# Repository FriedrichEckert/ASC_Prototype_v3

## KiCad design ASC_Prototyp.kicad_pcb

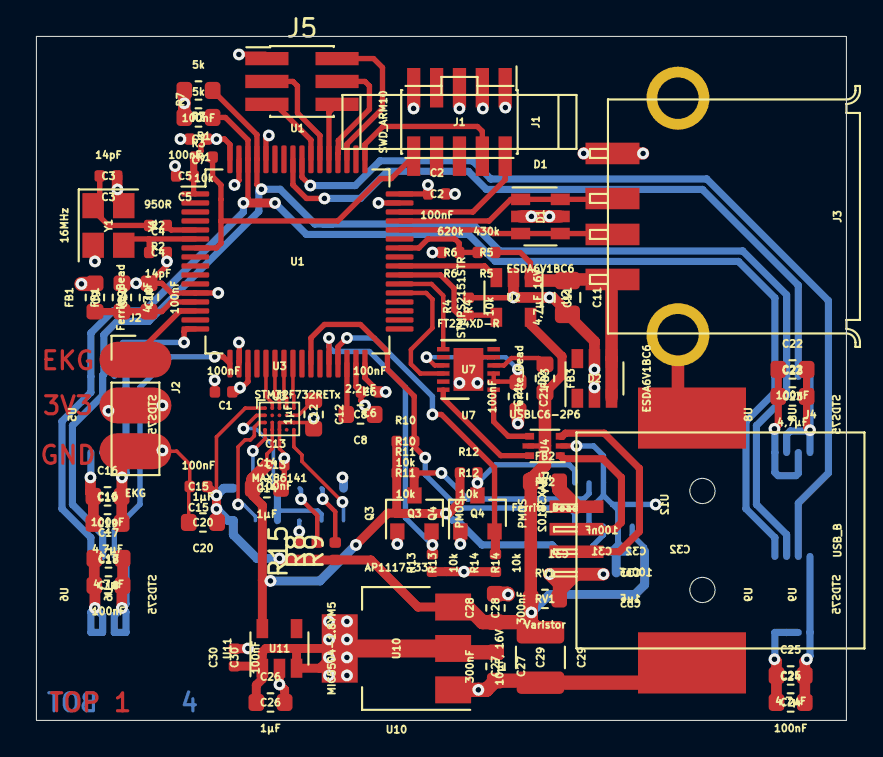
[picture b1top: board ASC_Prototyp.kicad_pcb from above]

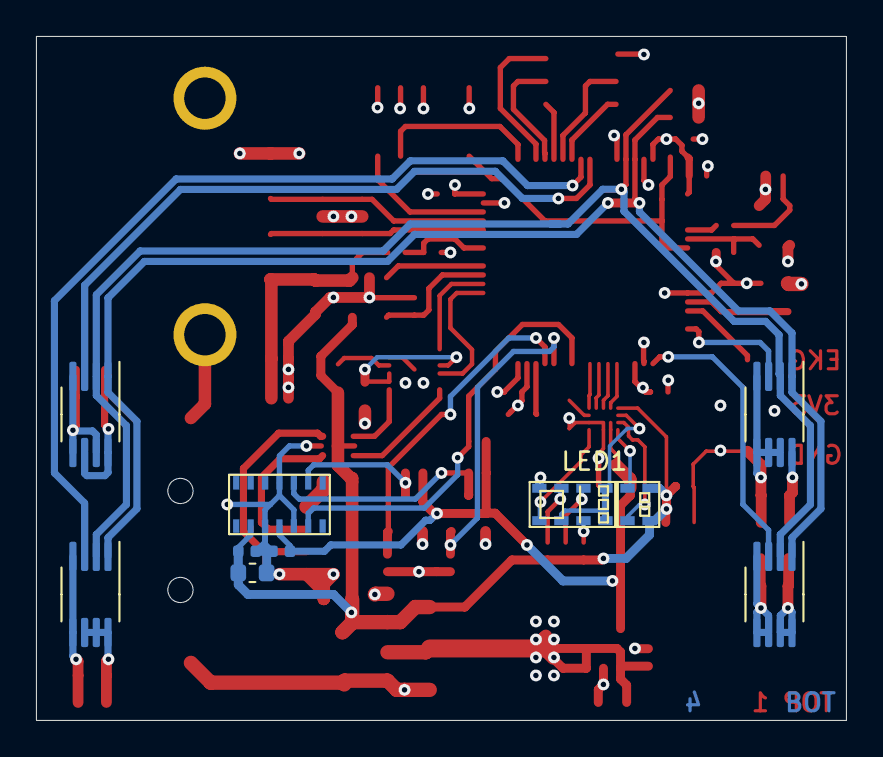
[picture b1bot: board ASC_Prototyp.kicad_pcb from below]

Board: 4 copper layers, 45.0 x 38.0 mm, 75 parts (9 on the bottom side), 56 nets.

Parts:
C1, C2, C5, C6, C7, C13, C15, C30, C31, C32: 100nF; C_0402_1005Metric
C3, C4: 14pF; C_0402_1005Metric
C8: 2,2µF; C_0603_1608Metric
C9, C17, C19, C23, C25: 4,7µF; C_0603_1608Metric
C10, C16, C18, C21, C22, C24: 100nF; C_0603_1608Metric
C11: 4,7µF 16V; C_0805_2012Metric
C12, C14, C20, C26, C33: 1µF; C_0603_1608Metric
C27, C28: 300nF; C_0603_1608Metric
C29: 10µF, 16V; C_1210_3225Metric
D1, D2: ESDA6V1BC6; SOT-23-6
FB1, FB2, FB3: Ferrite_Bead; L_0603_1608Metric
J1: SWD_ARM10
J2: EKG; PinHeader_1x03_P2.54mm_Vertical
J3: USB_A; USB_A_Buchse_87583-3010RPALF
J4: USB_B; USB_B_SMD
J5: Expander; PinHeader_2x03_P1.27mm_Vertical_SMD
LED1: SFH7060
Q3, Q4: PMOS; SOT-23
R1, R4, R10, R11, R12, R13, R14: 10k; R_0402_1005Metric
R2: 950R; R_0402_1005Metric
R3, R7: 5k; R_0603_1608Metric
R5: 430k; R_0402_1005Metric
R6: 620k; R_0402_1005Metric
R8, R9, R15: 0R; R_0402_1005Metric
RV1: Varistor; R_0603_1608Metric
U1: STM32F732RETx; LQFP-64_10x10mm_P0.5mm
U2: STMPS2151STR; SOT-23-5
U3: MAX86141; WLCSP-20_1.994x1.609mm_Layout5x4_P0.4mm_Modell
U4: USBLC6-2P6; SOT-666
U5, U6, U8, U9: STDS75; MSOP-8_3x3mm_P0.65mm
U7: FT234XD-R; DFN-12-1EP_3x3mm_P0.45mm_EP1.66x2.38mm
U10: AP1117-33; SOT-223-3_TabPin2
U11: MIC5504-1.8YM5; SOT-23-5
U12: MAX30102; MAX30102_LGA14
Y1: 16MHz; Crystal_SMD_3225-4Pin_3.2x2.5mm

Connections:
+1V8: C13.1, C14.1, C31.1, R10.1, R11.1, R12.1, U3.C2, U3.D2, U11.5, U12.11
+3V3: C1.1, C2.1, C5.1, C6.1, C7.1, C16.1, C17.1, C18.1, C19.1, C22.1, C23.1, C24.1, C25.1, C26.1, C27.1, C30.1, FB1.2, J1.1, J2.2, R1.1, R3.2, R7.2, R13.1, R14.1, U1.1, U1.19, U1.32, U1.48, U1.64, U5.8, U6.7, U6.8, U8.6, U8.8, U9.6, U9.7, U9.8, U10.2, U11.1, U11.3
+5V: C15.1, C20.1, C28.1, C29.1, C32.1, C33.1, FB2.1, FB3.2, LED1.1, LED1.12, R8.1, R9.1, R15.1, RV1.1, U2.5, U3.A1, U4.5, U10.3, U12.9
/EKG_ADC: J2.1, U1.14
/I2C1_SCL: R7.1, U1.61, U5.2, U6.2, U8.2, U9.2
/I2C1_SDA: R3.1, U1.62, U5.1, U6.1, U8.1, U9.1
/I2C2_SCL: Q3.2, R13.2, U1.28
/I2C2_SDA: Q4.2, R14.2, U1.29
/NRST: J1.10, R1.2, U1.7
/OXI2_~INT: R10.2, U1.26, U12.13
/OXI_MISO: U1.22, U3.A3
/OXI_MOSI: U1.23, U3.A4
/OXI_NSS: U1.24, U3.A5
/OXI_SCK: U1.21, U3.A2
/SPI3_MISO: J5.4, U1.52
/SPI3_MOSI: J5.6, U1.53
/SPI3_NSS1: J5.3, U1.54
/SPI3_NSS2: J5.5, U1.55
/SPI3_SCK: J5.2, U1.51
/SWCLK: J1.4, U1.49
/SWDIO: J1.2, U1.46
/UART6_RX: U1.38, U7.7
/UART6_TX: U1.37, U7.10
/USB_N: D1.3, D1.4, J3.2, U1.44
/USB_OverCurrent: U1.40, U2.3
/USB_P: D1.1, D1.6, J3.3, U1.45
/USB_PowerSwitchOn: R4.1, U1.39, U2.4
/VBUS_DET: R5.2, R6.1, U1.42
/VDD_A: C9.1, C10.1, FB1.1, U1.13
/~ALERT1: U1.16, U5.3
/~ALERT2: U1.17, U6.3
/~ALERT3: U1.57, U8.3
/~ALERT4: U1.56, U9.3
GND: C1.2, C2.2, C3.1, C4.2, C5.2, C6.2, C7.2, C8.1, C9.2, C10.2, C11.2, C12.2, C13.2, C14.2, C15.2, C16.2, C17.2, C18.2, C19.2, C20.2, C21.2, C22.2, C23.2, C24.2, C25.2, C26.2, C27.2, C28.2, C29.2, C30.2, C31.2, C32.2, C33.2, D1.2, D1.5, D2.2, D2.5, J1.3, J1.5, J1.9, J2.3, J3.4, J3.5, J4.4, J4.5, J5.1, LED1.6, Q3.1, Q4.1, R4.2, R6.2, RV1.2, U1.12, U1.18, U1.31, U1.47, U1.60, U1.63, U2.2, U3.C3, U3.C4, U3.C5, U3.D3, U4.2, U5.4, U5.5, U5.6, U5.7, U6.4, U6.5, U6.6, U7.5, U7.13, U8.4, U8.5, U8.7, U9.4, U9.5, U10.1, U11.2, U12.4, U12.10, U12.12, Y1.2, Y1.4
unnamed: C3.2, R2.2, Y1.1
unnamed: C4.1, U1.6, Y1.3
unnamed: C8.2, U1.30
unnamed: C11.1, D2.3, D2.4, J3.1, R5.1, U2.1
unnamed: C12.1, U3.B5
unnamed: C21.1, U7.2, U7.3, U7.9
unnamed: FB2.2, J4.1
unnamed: FB3.1, U7.4
unnamed: J4.2, U4.1
unnamed: J4.3, U4.3
unnamed: LED1.2, U3.D1
unnamed: LED1.4, R8.2
unnamed: LED1.5, R9.2
unnamed: LED1.7, U3.D5
unnamed: LED1.9, R15.2
unnamed: LED1.3, LED1.8, LED1.10, U3.B1
unnamed: LED1.11, U3.C1
unnamed: Q3.3, R11.2, U12.3
unnamed: Q4.3, R12.2, U12.2
unnamed: R2.1, U1.5
unnamed: U4.4, U7.1
unnamed: U4.6, U7.12

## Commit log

2021-04-29 added PDF Files for Layout
